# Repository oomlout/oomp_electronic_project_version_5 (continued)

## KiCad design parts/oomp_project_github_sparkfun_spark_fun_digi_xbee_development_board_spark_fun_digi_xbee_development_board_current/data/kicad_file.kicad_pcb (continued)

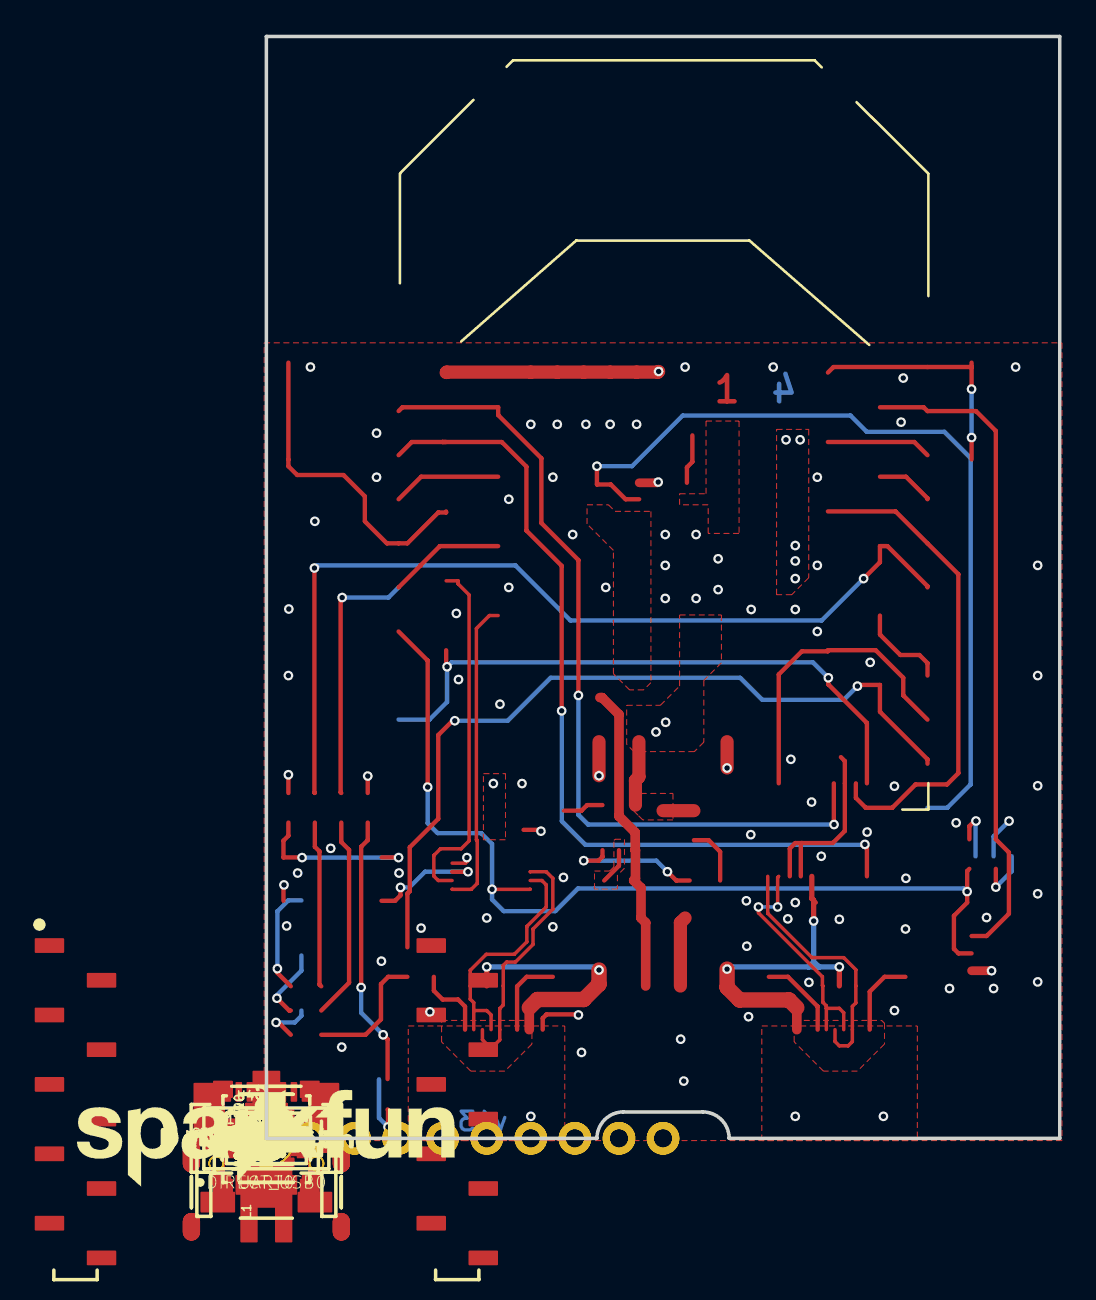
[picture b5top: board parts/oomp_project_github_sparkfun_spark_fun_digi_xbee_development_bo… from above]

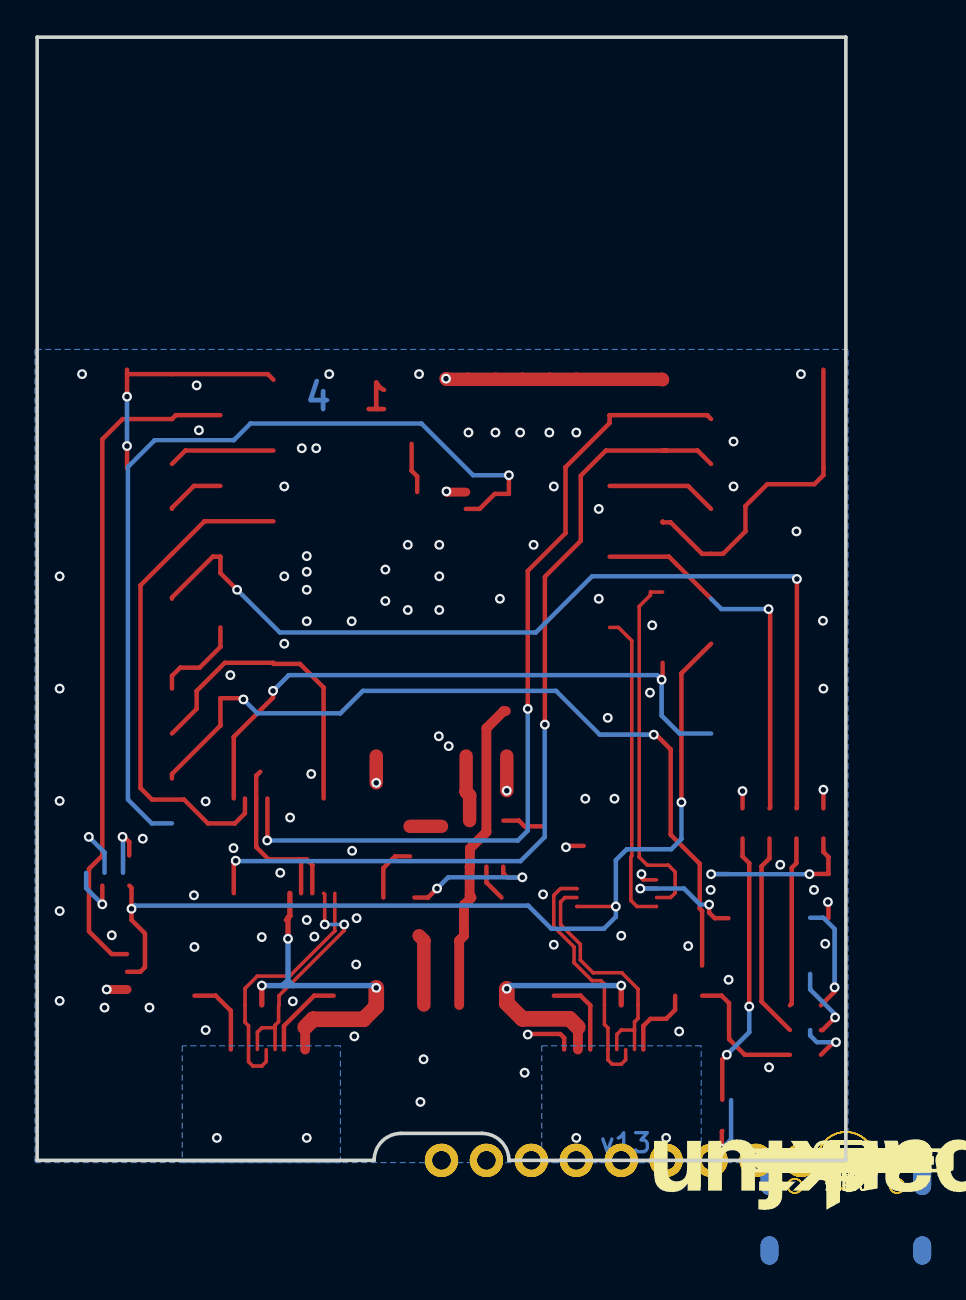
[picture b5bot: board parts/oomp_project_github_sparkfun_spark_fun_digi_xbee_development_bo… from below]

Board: 4 copper layers, 45.7 x 63.5 mm, 150 parts (44 on the bottom side), 55 nets.

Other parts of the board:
U$1: #D2#AD2#SCLK#19
U$2, U$17: ##RST##15
U$3: ##CS##19
U$4: ##CTS##25
U$5: ##DTR##27
U$6: #D1#AD1#SCL#8
U$7: ##RTS##24
U$8, U$21: #EN#17
U$9, U$44: #3V3#1
U$10: #D0#18
U$11, U$37: #VBAT#5
U$12: #D3#AD3#22
U$13: #D4#PICO#24
U$14: #POCI#D12#24
U$15: #TXO#D13#13
U$16: #RXI#D14#15
U$18: #RSSI#D10#17
U$19: CHG47
U$20, U$25, U$38, U$45: #GND#0
U$22: #SDA#D11#8
U$23, U$50: XBEE339
U$24, U$67: #NC#1
U$26: #I2C#33
U$27: #ALED#21
U$28: #PICO#23
U$29: #POCI#23
U$30: #RST#30
U$31: #RSSI#16
U$32: #DUSB#31
U$33: IO46
U$34: #SDA#7
U$35: #SHLD#740
U$36: #SHLD1#741
U$39: #D5#3
U$40: D03
U$41, U$46: #VIN#4
U$42: PWR26
U$43: ASC32
U$47: ##SLP##27
U$48, U$66: #NC#3
U$49: #I2C#31
U$51, U$70: DEVELOPMENT1345
U$52, U$71: BOARD1346
U$53: #D8##DTR##27
U$54: #PLED#20
U$55: #D0#AD0#18
U$56: #D5#ASSOC#24
U$57: #D6##RTS##24
U$58: #D7##CTS##25
U$59: #IOLED#23
U$60: #D9##SLP##27
U$61: SFE_LOGO_FLAME_.2
U$62: RSSI31
U$63: SFE_LOGO_NAME_.2
U$64: #RLED#22
U$65: UART32
U$68: DIRECT_USB33

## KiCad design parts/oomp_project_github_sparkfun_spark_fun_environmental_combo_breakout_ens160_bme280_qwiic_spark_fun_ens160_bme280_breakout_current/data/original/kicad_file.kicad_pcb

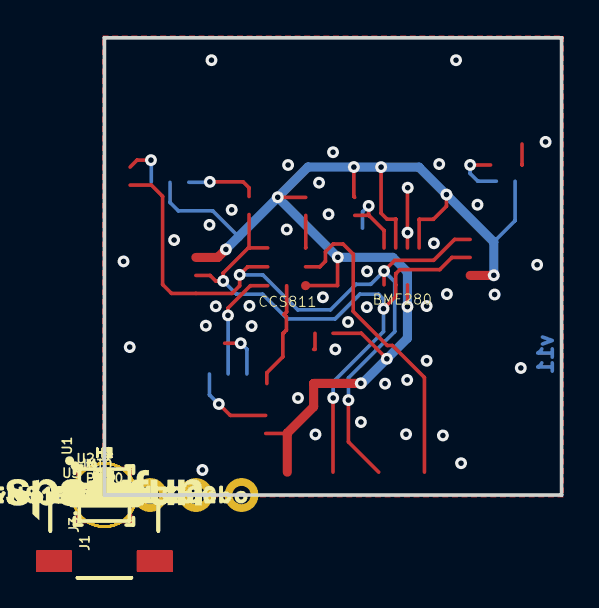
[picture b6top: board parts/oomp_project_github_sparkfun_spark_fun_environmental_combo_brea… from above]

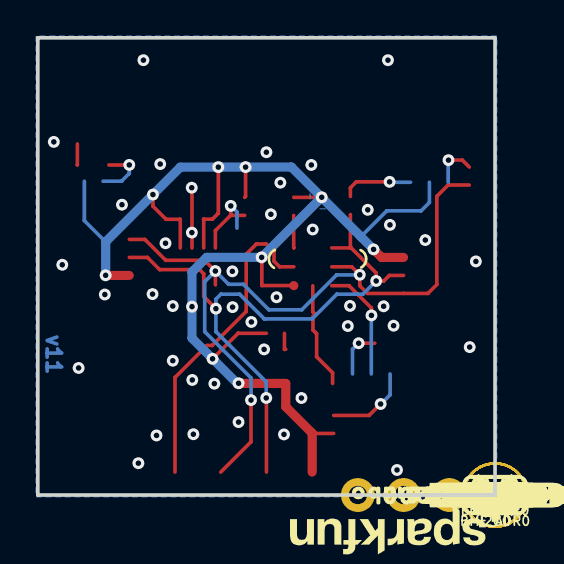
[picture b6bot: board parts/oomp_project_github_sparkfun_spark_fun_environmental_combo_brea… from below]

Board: 2 copper layers, 25.4 x 25.4 mm, 67 parts (25 on the bottom side), 16 nets.

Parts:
BME_ADR0: SMT-JUMPER_2_NO_SILK
C1, C3, C6: 0.1uF; 0402-TIGHT
C2, C5: 1.0uF; 0402-TIGHT
C4: 10uF; 0402-TIGHT
ENS_ADR0: JUMPER-SMT_3_1-NC_TRACE_SILK; SMT-JUMPER_3_1-NC_TRACE_SILK
FD1, FD2, FD3, FD4: FIDUCIAL1X2; FIDUCIAL-1X2
FRAME1: FRAME-LETTER; CREATIVE_COMMONS
H1, H2, H3, H4: STAND-OFF
I2C0: SMT-JUMPER_3_2-NC_TRACE_SILK
INT0: 1X01_NO_SILK_STAND
J1, J3: Qwiic Right Angle; JST04_1MM_RA
J4: PTH; 1X04_NO_SILK
LED0: SMT-JUMPER_2_NC_TRACE_SILK
LOGO1: SFE_LOGO_NAME.1_INCH; SFE_LOGO_NAME_.1
LOGO2: REVISION
LOGO3: SFE_LOGO_NAME.1_INCH; SFE_LOGO_NAME_.1@1
LOGO4: OSHW-LOGOS; OSHW-LOGO-S
PWR0: RED; LED-0603
R1, R6, R7, R8: 10k; 0402-TIGHT
R2: 4.7k; 0402-TIGHT
R3: 100k; 0402-TIGHT
R13, R14: 2.2k; 0402-TIGHT
U1: AP2127K-1.8V; SOT23-5
U2: ENS160; LGA-9
U3: BME280; LGA-8-2.5X2.5
U$1: #BME_ADR#0
U$2: #0X53#0
U$3: #0X52#0
U$4: ##INT##6
U$5: #ENS_ADR#0
U$6: #I2C#0
U$7, U$11: ENVIRONMENTAL_COMBO0
U$8: #SCL#4
U$9: #GND#2
U$10, U$12: ENS160_#_BME2800
U$13, U$61: DEFAULT0
U$14: #SDA#3
U$15: #PWR#0
U$16: OPEN#0X770
U$17: CLOSED#0X760
U$18: #LED#0
U$20, U$21: QWIIC_4MM
U$27, U$46: #3V3#874
U$45: #GND#864
U$47: #SDA#874
U$48: #SCL#875
U$51: ##INT##877
U$59: ORDERING_INSTRUCTIONS

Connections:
1.8V: C4.1, C5.1, U1.5, U2.P4
3.3V: C1.1, C2.1, C3.1, C6.1, I2C0.2, J1.2, J3.2, J4.2, LED0.1, R1.2, R3.2, R6.2, R8.2, U1.1, U2.P5, U3.2, U3.6, U3.8
ADDR: ENS_ADR0.2, U2.P3
GND: BME_ADR0.1, C1.2, C2.2, C3.2, C4.2, C5.2, C6.2, J1.1, J3.1, J4.1, R2.1, R7.1, U1.2, U2.P8, U2.P9, U3.1, U3.7
unnamed: ENS_ADR0.3, R8.1
unnamed: R1.1, U1.3
unnamed: I2C0.3, R13.2
unnamed: I2C0.1, R14.2
unnamed: PWR0.C, R2.2
unnamed: ENS_ADR0.1, R7.2
unnamed: LED0.2, PWR0.A
SCL: J1.4, J3.4, J4.4, R14.1, U2.P2, U3.4
SDA: J1.3, J3.3, J4.3, R13.1, U2.P1, U3.3
SDO/ADR: BME_ADR0.2, R3.1, U3.5
~CS: R6.1, U2.P7
~INT: INT0.1, U2.P6
